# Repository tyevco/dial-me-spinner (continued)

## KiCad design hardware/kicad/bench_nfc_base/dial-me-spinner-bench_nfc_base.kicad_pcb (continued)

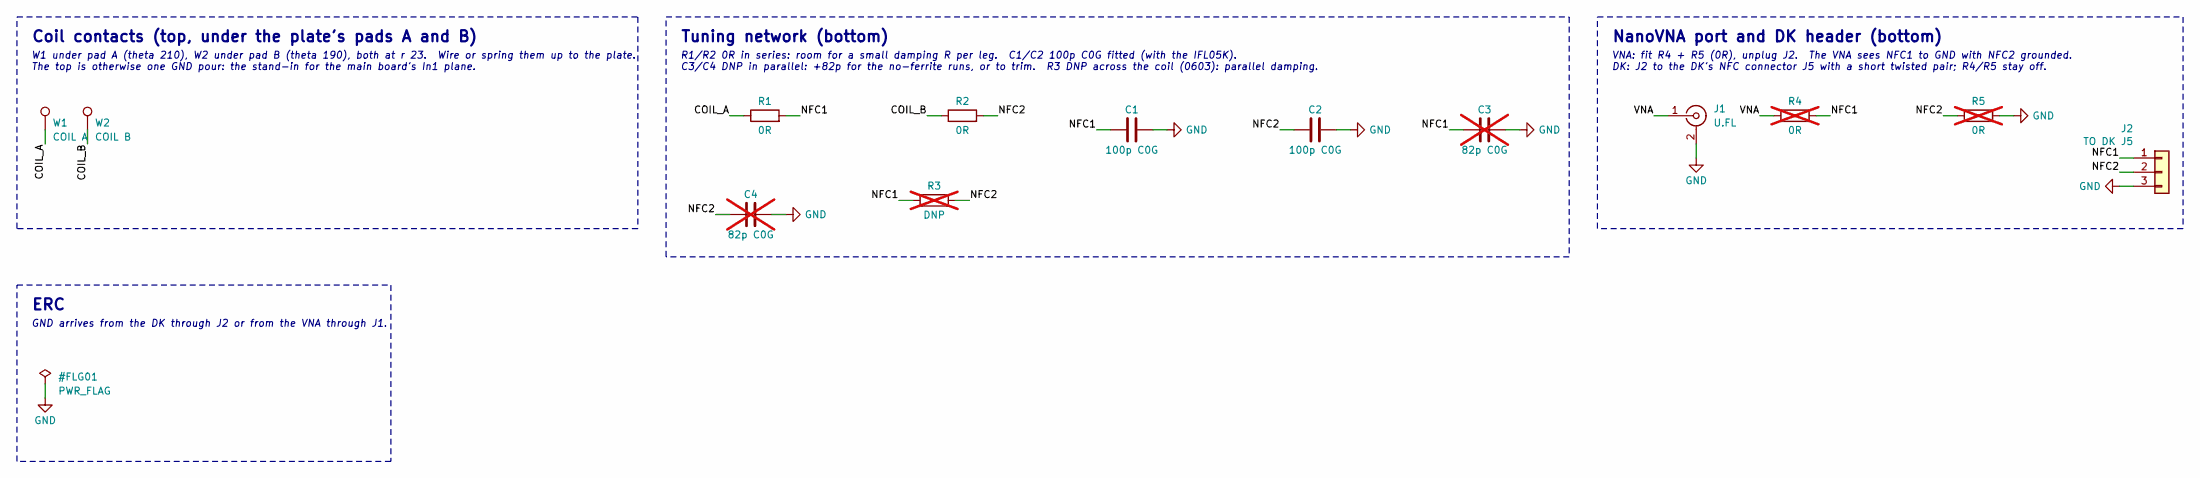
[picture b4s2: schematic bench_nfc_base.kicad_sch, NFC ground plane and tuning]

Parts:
C1, C2: 100p C0G; C_0402_1005Metric; MPN 0402CG101J500NT; LCSC C1546
C3, C4: 82p C0G; C_0402_1005Metric; MPN 0402CG820J500NT; LCSC C45501; not fitted
J1: U.FL; U.FL_Hirose_U.FL-R-SMT-1_Vertical; MPN U.FL-R-SMT-1(10); LCSC C88373
J2: TO DK J5; PinHeader_1x03_P2.54mm_Vertical
R1, R2: 0R; R_0402_1005Metric; MPN 0402WGF0000TCE; LCSC C17168
R3: DNP; R_0603_1608Metric; not fitted
R4, R5: 0R; R_0402_1005Metric; MPN 0402WGF0000TCE; LCSC C17168; not fitted
W1: COIL A; TestPoint_THTPad_2.0x2.0mm_Drill1.0mm
W2: COIL B; TestPoint_THTPad_2.0x2.0mm_Drill1.0mm

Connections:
/NFC ground plane and tuning/COIL_A: R1.1, W1.1
/NFC ground plane and tuning/COIL_B: R2.1, W2.1
/NFC ground plane and tuning/NFC1: C1.1, C3.1, J2.1, R1.2, R3.1, R4.2
/NFC ground plane and tuning/NFC2: C2.1, C4.1, J2.2, R2.2, R3.2, R5.1
/NFC ground plane and tuning/VNA: J1.1 (In), R4.1
GND: C1.2, C2.2, C3.2, C4.2, J1.2 (Ext), J2.3, R5.2

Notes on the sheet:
Coil contacts (top, under the plate's pads A and B)
W1 under pad A (theta 210), W2 under pad B (theta 190), both at r 23. Wire or spring them up to the plate. The top is otherwise one GND pour: the stand-in for the main board's In1 plane.
Tuning network (bottom)
R1/R2 0R in series: room for a small damping R per leg. C1/C2 100p C0G fitted (with the IFL05K). C3/C4 DNP in parallel: +82p for the no-ferrite runs, or to trim. R3 DNP across the coil (0603): parallel damping.
NanoVNA port and DK header (bottom)
VNA: fit R4 + R5 (0R), unplug J2. The VNA sees NFC1 to GND with NFC2 grounded. DK: J2 to the DK's NFC connector J5 with a short twisted pair; R4/R5 stay off.
ERC
GND arrives from the DK through J2 or from the VNA through J1.

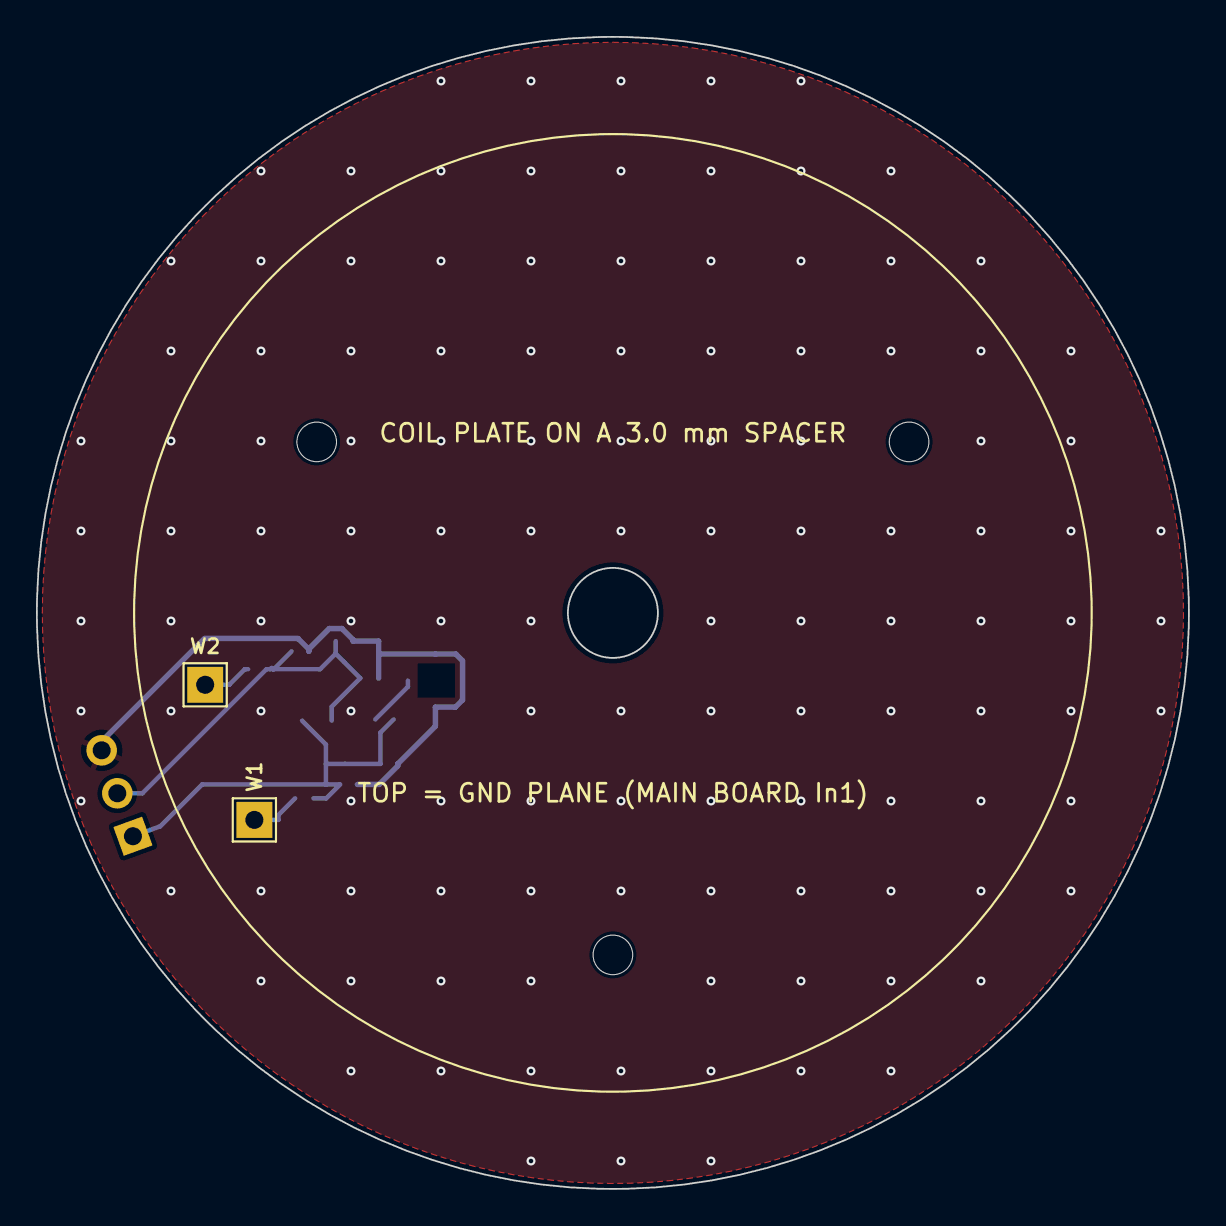
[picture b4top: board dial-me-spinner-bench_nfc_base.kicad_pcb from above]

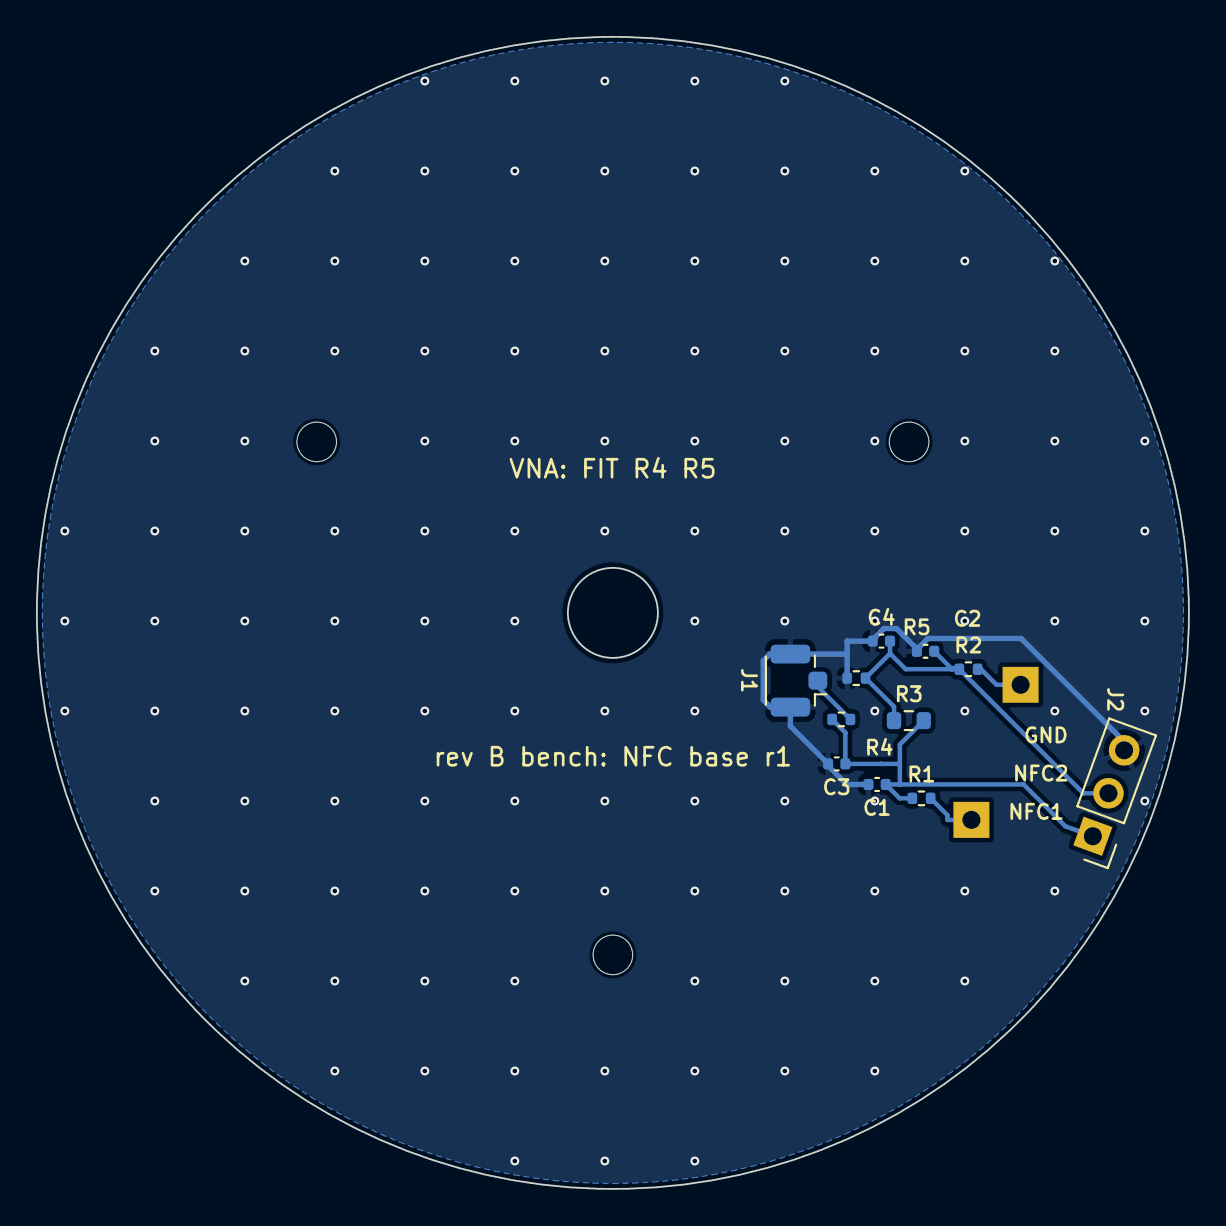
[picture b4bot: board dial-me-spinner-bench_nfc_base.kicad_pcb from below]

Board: 2 copper layers, 64.0 x 64.0 mm, 16 parts (11 on the bottom side), 6 nets.

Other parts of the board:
H1, H2, H3: MountingHole_2.2mm_M2

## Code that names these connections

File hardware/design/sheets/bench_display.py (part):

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    "16": "DISP_VBAT_EN",  # D1   P1.02  (rev A OLED_VCC_EN)
    "17": None,            # D2   P1.03
    "18": None,            # D3   P1.04
    "19": "DISP_VCI_EN",   # D4   P1.05  (rev B pin, study §7.1)
    "20": None,            # D5   P1.06
    "21": None,            # D6   P1.07
    "22": "DISP_SCK_DK",   # D7   P1.08  FULL SPEED
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    "28": None,            # D13  P1.15
    "9": None,             # A0   P0.03
    "10": "DISP_SIO0_DK",  # A1   P0.04  FULL SPEED
    "11": "TP_INT",        # A2   P0.28  (rev B pin)
    "12": "TP_RST_N",      # A3   P0.29  (rev B pin)
    "13": "DISP_SIO1",     # A4   P0.30  read-back only (ID / status at a reduced clock)
    "14": "DISP_TE",       # A5   P0.31  (rev B pin)
    "31": "I2C_SDA",       # SDA  P0.26
    "32": "I2C_SCL",       # SCL  P0.27
    "2": "VDD_DK",         # IOREF = the DK's VDD (3.0 V as shipped)
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    d.add("J1", "MCU_Module:Arduino_UNO_R3", "nRF52840-DK", "Module:Arduino_UNO_R3",
          pins=DK_PINS, in_bom=False,
          description="Arduino Uno R3 shield headers (hand-fitted stacking headers), nRF52840-DK PCA10056")
    d.add("R41", "Device:R", "0R", R0402, pins={"1": "DK_3V3", "2": "VDD_DK"}, dnp=True, fields=R0,
          description="Fit only if the DK leaves IOREF unconnected")

    d.group("Panel connector (FH26W-31S, connector pin = 32 - panel pin)",
            "Silk marks PANEL PIN 1 at connector pin 31.  Bottom contact: FPC contacts face the board.\n"
            "MTP_PWR (panel 13) open; MIPI pairs (panel 23-24, 26-27, 29-30) open.\n"
            "Decoupling at the connector pins: VBAT 10u + 100n, VCI 4.7u + 100n, IOVCC 1u + 100n, TP_VDD 1u + 100n.")
    d.add("J2", "Connector_Generic_MountingPin:Conn_01x31_MountingPin", "FH26W-31S-0.3SHW(60)", FH26_FP,
          pins={**{str(32 - p): n for p, n in PANEL_PINS.items()}, "MP": "GND"},
          datasheet=SPEC_DS,
          fields={"MPN": "FH26W-31S-0.3SHW(60)", "Manufacturer": "HIROSE", "LCSC": "C2973806"})
    d.add("C1", "Device:C", "10u", C0603, pins={"1": "DISP_VBAT", "2": "GND"}, fields=C10U)
    d.add("C2", "Device:C", "100n", C0402, pins={"1": "DISP_VBAT", "2": "GND"}, fields=C100N)
    d.add("C3", "Device:C", "4.7u", C0805, pins={"1": "VCI", "2": "GND"}, fields=C4U7)
    d.add("C4", "Device:C", "100n", C0402, pins={"1": "VCI", "2": "GND"}, fields=C100N)
    d.add("C5", "Device:C", "1u", C0402, pins={"1": "IOVCC", "2": "GND"}, fields=C1U)
    d.add("C6", "Device:C", "100n", C0402, pins={"1": "IOVCC", "2": "GND"}, fields=C100N)
    d.add("C7", "Device:C", "1u", C0402, pins={"1": "TP_VDD", "2": "GND"}, fields=C1U)
    d.add("C8", "Device:C", "100n", C0402, pins={"1": "TP_VDD", "2": "GND"}, fields=C100N)

    d.group("Panel VBAT: external source or DK VDD, through the rev B load switch",
            "J3 takes a PPK2 in source-meter mode for the 3.0-4.5 V sweep and the current-vs-content runs.\n"
            "J4 selects VBAT_IN: 1-2 = J3 (external), 2-3 = DK VDD (3.0 V, below the pin table's 3.7 V minimum).\n"
            "U1 is the TPS22917 rev B keeps (U21, renamed DISP_VBAT_EN): same CT and QOD wiring as rev A.\n"
            "R1 (DNP) bypasses U1 to rule it out.")
    d.add("J3", "Connector_Generic:Conn_01x02", "VBAT EXT", "Connector_PinHeader_2.54mm:PinHeader_1x02_P2.54mm_Vertical",
          pins={"1": "VBAT_EXT", "2": "GND"}, in_bom=False)
    d.add("J4", "Connector_Generic:Conn_01x03", "VBAT SEL", "Connector_PinHeader_2.54mm:PinHeader_1x03_P2.54mm_Vertical",
          pins={"1": "VBAT_EXT", "2": "VBAT_IN", "3": "VDD_DK"}, in_bom=False)
    d.add("U1", "Power_Management:TPS22917DBV", "TPS22917DBVR", "Package_TO_SOT_SMD:SOT-23-6",
          pins={"VIN": "VBAT_IN", "GND": "GND", "ON": "DISP_VBAT_EN", "CT": "DISP_LSW_CT",
                "QOD": "DISP_VBAT", "VOUT": "DISP_VBAT"},
          fields={"MPN": "TPS22917DBVR", "Manufacturer": "Texas Instruments", "LCSC": "C2681320"})
    d.add("C9", "Device:C", "1n", C0402, pins={"1": "DISP_LSW_CT", "2": "VBAT_IN"}, fields=C1N)
    d.add("C10", "Device:C", "10u", C0603, pins={"1": "VBAT_IN", "2": "GND"}, fields=C10U,
          description="U1 VIN bypass")
    d.add("R2", "Device:R", "100k", R0402, pins={"1": "DISP_VBAT_EN", "2": "GND"}, fields=R100K)
    d.add("R1", "Device:R", "0R", R0402, pins={"1": "VBAT_IN", "2": "DISP_VBAT"}, dnp=True, fields=R0)

    d.group("Panel logic rails from DK VDD, each separable",
            "J5 shunt carries VCI + IOVCC + TP_VDD: remove it and put a PPK2 (ammeter) across to log the logic current.\n"
            "R3-R5 split the three rails so any one can be fed or measured on its own.")
    d.add("J5", "Connector_Generic:Conn_01x02", "IDD LOGIC", "Connector_PinHeader_2.54mm:PinHeader_1x02_P2.54mm_Vertical",
          pins={"1": "VDD_DK", "2": "VDD_PANEL"}, in_bom=False)
    d.add("R3", "Device:R", "0R", R0402, pins={"1": "VDD_PANEL", "2": "VCI"}, fields=R0)
    d.add("R4", "Device:R", "0R", R0402, pins={"1": "VDD_PANEL", "2": "IOVCC"}, fields=R0)
    d.add("R5", "Device:R", "0R", R0402, pins={"1": "VDD_PANEL", "2": "TP_VDD"}, fields=R0)

    d.group("Display control and the 32 MHz lines",
            "R6/R7 0R at the header: swap for 22-33R if the SCK/SIO0 edges ring (CO5300 needs <= 3.5 ns 20-80 %).\n"
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            "DISP_RES_N 1M pull-down and DISP_VCI_EN 100k pull-down hold the panel off while the DK resets.\n"
            "SIO1 (DCX) reads back on A4, a low-frequency pin: read ID/status at a reduced clock only.\n"
            "SIO2/SIO3 are unused by the single-lane driver: 10k pull-downs, TP7/TP8 for a later QSPI test.")
    d.add("R6", "Device:R", "0R", R0402, pins={"1": "DISP_SCK_DK", "2": "DISP_SCK"}, fields=R0)
    d.add("R7", "Device:R", "0R", R0402, pins={"1": "DISP_SIO0_DK", "2": "DISP_SIO0"}, fields=R0)
    d.add("R8", "Device:R", "1M", R0402, pins={"1": "DISP_RES_N", "2": "GND"}, fields=R1M)
    d.add("R9", "Device:R", "100k", R0402, pins={"1": "DISP_VCI_EN", "2": "GND"}, fields=R100K)
    d.add("R10", "Device:R", "100k", R0402, pins={"1": "IOVCC", "2": "DISP_CS_N"}, fields=R100K)
    d.add("R11", "Device:R", "100k", R0402, pins={"1": "DISP_SIO1", "2": "GND"}, fields=R100K)
    d.add("R12", "Device:R", "10k", R0402, pins={"1": "DISP_SIO2", "2": "GND"}, fields=R10K)
    d.add("R13", "Device:R", "10k", R0402, pins={"1": "DISP_SIO3", "2": "GND"}, fields=R10K)
    for ref, net in (("TP1", "DISP_SCK"), ("TP2", "DISP_SIO0"), ("TP3", "DISP_CS_N"), ("TP4", "DISP_TE"),
                     ("TP5", "GND"), ("TP6", "GND"), ("TP7", "DISP_SIO2"), ("TP8", "DISP_SIO3")):
        d.add(ref, "Connector:TestPoint", net, TP_FP, pins={"1": net}, in_bom=False)
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            "1.8 V option (the Huaxin/Viewe drawings): remove R14/R15/R16, fit U2, U3, C11, C12, R17, R18, R19.\n"
            "In 1.8 V mode TP_INT and TP_RST_N are NOT shifted: TP_INT at 1.8 V is below the nRF's 0.7 VDD = 2.1 V\n"
            "VIH, and the nRF would drive TP_RST_N to 3.0 V.  That mode answers 'does the bus work', not 'is it done'.")
    d.add("R14", "Device:R", "0R", R0402, pins={"1": "TP_SDA", "2": "I2C_SDA"}, fields=R0)
    d.add("R15", "Device:R", "0R", R0402, pins={"1": "TP_SCL", "2": "I2C_SCL"}, fields=R0)
    d.add("R16", "Device:R", "0R", R0402, pins={"1": "VDD_PANEL", "2": "TP_VIO"}, fields=R0)
    d.add("R20", "Device:R", "4.7k", R0402, pins={"1": "VDD_DK", "2": "I2C_SDA"}, fields=R4K7)
    d.add("R21", "Device:R", "4.7k", R0402, pins={"1": "VDD_DK", "2": "I2C_SCL"}, fields=R4K7)
    d.add("R22", "Device:R", "100k", R0402, pins={"1": "TP_VIO", "2": "TP_INT"}, fields=R100K)
    d.add("R23", "Device:R", "100k", R0402, pins={"1": "TP_VIO", "2": "TP_RST_N"}, fields=R100K)
    d.add("U2", "Interface:PCA9306DC", "PCA9306DCUR", "Package_SO:VSSOP-8_2.3x2mm_P0.5mm",
          pins={"VREF1": "TP_VIO", "VREF2": "PCA_EN", "EN": "PCA_EN", "GND": "GND",
                "SCL1": "TP_SCL", "SDA1": "TP_SDA", "SCL2": "I2C_SCL", "SDA2": "I2C_SDA"},
          dnp=True, fields={"MPN": "PCA9306DCUR", "Manufacturer": "Texas Instruments", "LCSC": "C33196"})
    d.add("R17", "Device:R", "200k", R0402, pins={"1": "VDD_DK", "2": "PCA_EN"}, dnp=True, fields=R200K,
          description="PCA9306 VREF2/EN bias (datasheet: 200k to the high-side supply)")
    d.add("R18", "Device:R", "4.7k", R0402, pins={"1": "TP_VIO", "2": "TP_SDA"}, dnp=True, fields=R4K7)
    d.add("R19", "Device:R", "4.7k", R0402, pins={"1": "TP_VIO", "2": "TP_SCL"}, dnp=True, fields=R4K7)
    d.add("U3", "Regulator_Linear:AP2112K-1.8", "AP2112K-1.8TRG1", "Package_TO_SOT_SMD:SOT-23-5",
          pins={"VIN": "VDD_PANEL", "EN": "VDD_PANEL", "GND": "GND", "NC": None, "VOUT": "TP_VIO"},
          dnp=True, fields={"MPN": "AP2112K-1.8TRG1", "Manufacturer": "Diodes Incorporated", "LCSC": "C176944"})
    d.add("C11", "Device:C", "1u", C0402, pins={"1": "VDD_PANEL", "2": "GND"}, dnp=True, fields=C1U)
    d.add("C12", "Device:C", "1u", C0402, pins={"1": "TP_VIO", "2": "GND"}, dnp=True, fields=C1U)

    d.group("ERC power flags",
            "Every rail here arrives from a header or through a jumper / 0R link, which ERC cannot see as a source.")
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
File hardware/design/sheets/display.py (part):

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def build(d):
    d.sheet(*SHEET)
    # Layout notes (generator-specific): 2-pin parts whose pins carry long power names
    # (+13V_OLED, OLED_VIN) are drawn vertical (rot=0) with the long name on the bottom pin;
    # vertical parts alternate with horizontal ones so their side fields never collide.

    # ------------------------------------------------------------------ panel
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          fields={"MPN": "AFC01-S30FCA-00", "Manufacturer": "JUSHUO", "LCSC": "C262671",
                  "Mates_With": "NHD-1.5-128128G (Newhaven) / AOC128128A0-1.50W (Orient)",
                  "Panel_Datasheet": NHD_DS})
    d.add("R20", "Device:R", "1M", R0402, pins={"1": "OLED_RES_N", "2": "GND"},
          fields={"MPN": "0402WGF1004TCE", "Manufacturer": "UNI-ROYAL", "LCSC": "C26083"})
    d.add("#FLG21", "power:PWR_FLAG", "PWR_FLAG", "", pins={"1": "+13V_OLED"}, in_bom=False, on_board=False)

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            "C39 = boost output cap on +13V_OLED: place it at D21 / U20 GND, not at the ZIF.\n"
            "No bleeders or QOD switches on +3V3 / +13V_OLED (VCC must float when off).", 182))
    d.add("C32", "Device:C_Polarized", "4.7u/25V Ta", "Capacitor_Tantalum_SMD:CP_EIA-3216-18_Kemet-A",
          pins={"1": "OLED_VCOMH", "2": "GND"},
          description="VCOMH (FPC pin 3) tantalum, + to VCOMH",
          fields={"MPN": "TAJA475K025RNJ", "Manufacturer": "KYOCERA AVX", "LCSC": "C7189"})
    d.add("C30", "Device:C", "10u/25V", C0805, rot=0, pins={"1": "GND", "2": "+13V_OLED"},
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    d.add("C31", "Device:C", "100n/50V", C0402, rot=0, pins={"1": "GND", "2": "+13V_OLED"},
          description="VCC (FPC pin 2) HF decoupling",
          fields={"MPN": "CL05B104KB54PNC", "Manufacturer": "Samsung Electro-Mechanics", "LCSC": "C307331"})
    d.add("C34", "Device:C", "1u", C0402, pins={"1": "OLED_VDD", "2": "GND"},
          description="VDD (FPC pin 26, internal regulator output)",
          fields={"MPN": "CL05A105KA5NQNC", "Manufacturer": "Samsung Electro-Mechanics", "LCSC": "C52923"})
    d.add("C39", "Device:C", "4.7u/25V", C0805, rot=0, pins={"1": "GND", "2": "+13V_OLED"},
          description="Boost output capacitor (place at D21 cathode / U20 GND)",
          fields={"MPN": "CL21A475KAQNNNE", "Manufacturer": "Samsung Electro-Mechanics", "LCSC": "C1779"})
    d.add("C35", "Device:C", "4.7u/25V", C0805, pins={"1": "GND", "2": "+3V3"},
          description="VCI (FPC pin 27) bulk",
          fields={"MPN": "CL21A475KAQNNNE", "Manufacturer": "Samsung Electro-Mechanics", "LCSC": "C1779"})
    d.add("C36", "Device:C", "100n", C0402, rot=0, pins={"1": "GND", "2": "+3V3"},
          description="VCI (FPC pin 27) HF decoupling",
          fields={"MPN": "CL05B104KO5NNNC", "Manufacturer": "Samsung Electro-Mechanics", "LCSC": "C1525"})

    d.group("IREF and VSL networks",
            "IREF: R = (VCC - 6 V) / 12.5 uA = 560k at 13 V (recompute if VCC changes).\n"
            "VSL: 50 ohm 1/4 W + ~1.4 V: BAV99 as 2 series diodes (pin 1 A1, pin 3 mid NC, pin 2 K2).")
    d.add("R21", "Device:R", "560k", R0402, pins={"1": "OLED_IREF", "2": "GND"},
          fields={"MPN": "0402WGF5603TCE", "Manufacturer": "UNI-ROYAL", "LCSC": "C132339"})
    d.add("R22", "Device:R", "51R 1/4W", R1206, pins={"1": "OLED_VSL", "2": "OLED_VSL_D"},
          fields={"MPN": "1206W4F510JT5E", "Manufacturer": "UNI-ROYAL", "LCSC": "C18019"})
    d.add("D20", "Diode:BAV99", "BAV99", SOT23,
          pins={"1": "OLED_VSL_D", "2": "GND", "3": None},
          fields={"MPN": "BAV99,215", "Manufacturer": "Nexperia", "LCSC": "C2500"})

    # ------------------------------------------------------------------ boost
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            "(Replaces the AO3401A/2N7002 disconnect, which had no real dV/dt control - review SCH-1.)\n"
            "LAYOUT: L20 and the SW node >= 10 mm from the TMAG5273 and the magnet track.", 180))
    d.add("U21", "Power_Management:TPS22917DBV", "TPS22917DBVR", "Package_TO_SOT_SMD:SOT-23-6",
          pins={"VIN": "VSYS", "GND": "GND", "ON": "OLED_VCC_EN", "CT": "OLED_LSW_CT", "QOD": "OLED_VIN", "VOUT": "OLED_VIN"},
          fields={"MPN": "TPS22917DBVR", "Manufacturer": "Texas Instruments", "LCSC": "C2681320"})
    d.add("C37", "Device:C", "1n/50V", C0402, pins={"1": "OLED_LSW_CT", "2": "VSYS"},
          fields={"MPN": "0402B102K500NT", "Manufacturer": "FH", "LCSC": "C1523"})
    d.add("C41", "Device:C", "10u/25V", "Capacitor_SMD:C_0603_1608Metric", pins={"1": "VSYS", "2": "GND"},
          description="U21 VIN bypass",
          fields={"MPN": "CL10A106MA8NRNC", "Manufacturer": "Samsung Electro-Mechanics", "LCSC": "C96446"})
    d.add("C38", "Device:C", "4.7u/25V", C0805, rot=0, pins={"1": "GND", "2": "OLED_VIN"},
          description="Boost input capacitor (place at U20 VIN/GND)",
          fields={"MPN": "CL21A475KAQNNNE", "Manufacturer": "Samsung Electro-Mechanics", "LCSC": "C1779"})
    d.add("R25", "Device:R", "100k", R0402, pins={"1": "OLED_VCC_EN", "2": "GND"},
          fields={"MPN": "0402WGF1003TCE", "Manufacturer": "UNI-ROYAL", "LCSC": "C25741"})
    d.add("L20", "Device:L", "10u", "Inductor_SMD:L_Sunlord_SWPA3015S",
          rot=0, pins={"1": "OLED_BST_SW", "2": "OLED_VIN"},
          fields={"MPN": "SWPA3015S100MT", "Manufacturer": "Sunlord", "LCSC": "C45403"})

    d.group("13 V boost: TPS61040, rectifier, FB divider", _pad(
            "VOUT = 1.233 V x (1 + 499k / 52.3k) = 13.00 V (0.5 % / 0.1 % divider); CFF C40 33 pF across R26 (tune 22-100 pF).\n"
            "EN tied to OLED_VIN: the input disconnect does the switching.  L 10 uH, Isat 0.72 A rated (0.92 A typ; peak need 0.49 A).\n"
            "LAYOUT: tight CIN-L-SW-GND and SW-D-COUT-GND loops; R26/R27/C40 at the FB pin, away from SW.", 150))
    d.add("R27", "Device:R", "52.3k 0.1%", R0402, pins={"1": "GND", "2": "OLED_BST_FB"},
          fields={"MPN": "RT0402BRD0752K3L", "Manufacturer": "YAGEO", "LCSC": "C852832"})
    d.add("R26", "Device:R", "499k 0.5%", R0402, rot=0, pins={"1": "OLED_BST_FB", "2": "+13V_OLED"},
          fields={"MPN": "RC0402DR-07499KL", "Manufacturer": "YAGEO", "LCSC": "C4167968"})
    d.add("U20", "Regulator_Switching:TPS61040DBV", "TPS61040DBVR", "Package_TO_SOT_SMD:SOT-23-5",
          pins={"VIN": "OLED_VIN", "EN": "OLED_VIN", "GND": "GND", "SW": "OLED_BST_SW", "FB": "OLED_BST_FB"},
          datasheet=TPS_DS,
          fields={"MPN": "TPS61040DBVR", "Manufacturer": "Texas Instruments", "LCSC": "C7722"})
    d.add("C40", "Device:C", "33p C0G", C0402, rot=0, pins={"1": "OLED_BST_FB", "2": "+13V_OLED"},
          fields={"MPN": "0402CG330J500NT", "Manufacturer": "FH (Fenghua)", "LCSC": "C1562"})
    d.add("D21", "dial_spinner:B5819W_SOD123", "B5819W", "Diode_SMD:D_SOD-123",
          pins={"A": "OLED_BST_SW", "K": "+13V_OLED"},
          fields={"MPN": "B5819W SL", "Manufacturer": "Jiangsu Changjing (CJ)", "LCSC": "C8598"})

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
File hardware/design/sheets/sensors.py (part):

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    d.add("C51", "Device:C", "1u", C0402, pins={"1": "GND", "2": "+3V3"},
          fields={"MPN": "CL05A105KA5NQNC", "Manufacturer": "Samsung Electro-Mechanics", "LCSC": "C52923"})
    d.add("U30", "dial_spinner:TMAG5273", "TMAG5273A2QDBVR", "Package_TO_SOT_SMD:SOT-23-6",
          pins={"1": "TMAG_SCL", "6": "TMAG_SDA", "5": "TMAG_INT_N", "4": "+3V3", "2": "GND", "3": "GND"},
          fields={"MPN": "TMAG5273A2QDBVR", "Manufacturer": "Texas Instruments", "LCSC": "C3715882"})

    d.group("Encoder ESD (floating 316L ring 2.4 mm below)",
            "The flywheel is a touchable, electrically floating metal ring passing under U30.\n"
            "U32 clamps TMAG_SCL/SDA/INT_N right at U30 (short GND return via next to U30).")
    d.add("U32", "Power_Protection:TPD4E05U06DQA", "TPD4E05U06DQAR", "Package_SON:USON-10_2.5x1.0mm_P0.5mm",
          pins={"1": "TMAG_SCL", "2": "TMAG_SDA", "4": "TMAG_INT_N", "5": None, "3": "GND",
                "6": None, "7": None, "9": None, "10": None},
          fields={"MPN": "TPD4E05U06DQAR", "Manufacturer": "Texas Instruments", "LCSC": "C138714"},
          datasheet="https://www.ti.com/lit/ds/symlink/tpd4e05u06.pdf")

    d.group("Encoder bus pull-ups (dedicated TWIM0)",
            "4.7k SCL/SDA; 47k on open-drain INT (10 us pulses / latched)")
    d.add("R50", "Device:R", "4.7k", R0402, pins={"1": "+3V3", "2": "TMAG_SCL"},
          fields={"MPN": "0402WGF4701TCE", "Manufacturer": "UNI-ROYAL", "LCSC": "C25900"})
    d.add("R51", "Device:R", "4.7k", R0402, pins={"1": "+3V3", "2": "TMAG_SDA"},
          fields={"MPN": "0402WGF4701TCE", "Manufacturer": "UNI-ROYAL", "LCSC": "C25900"})
    d.add("R52", "Device:R", "47k", R0402, pins={"1": "+3V3", "2": "TMAG_INT_N"},
          fields={"MPN": "0402WGF4702TCE", "Manufacturer": "UNI-ROYAL", "LCSC": "C25792"})

    # ---------------------------------------------------------------- IMU
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    d.add("C54", "Device:C", "100n", C0402, pins={"1": "GND", "2": "+3V3"},
          fields={"MPN": "CL05B104KO5NNNC", "Manufacturer": "Samsung Electro-Mechanics", "LCSC": "C1525"})
    d.add("U31", "dial_spinner:LIS2DW12", "LIS2DW12TR", "Package_LGA:LGA-12_2x2mm_P0.5mm",
          pins={"1": "I2C_SCL", "4": "I2C_SDA", "2": "+3V3", "3": "+3V3",
                "12": "IMU_INT1", "11": "IMU_INT2", "5": None,
                "9": "+3V3", "10": "+3V3", "6": "GND", "8": "GND", "7": "GND"},
          fields={"MPN": "LIS2DW12TR", "Manufacturer": "STMicroelectronics", "LCSC": "C189624"})
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    # ---------------------------------------------------------------- pull-ups
    d.group("System I2C + link signal pull-ups (the only ones on the board)",
            "System I2C goes to IMU + BQ25180 (0x6A, via link). CHG_INT_N / BTN_N are open drain on the base board.")
    d.add("R53", "Device:R", "4.7k", R0402, pins={"1": "+3V3", "2": "I2C_SCL"},
          fields={"MPN": "0402WGF4701TCE", "Manufacturer": "UNI-ROYAL", "LCSC": "C25900"})
    d.add("R54", "Device:R", "4.7k", R0402, pins={"1": "+3V3", "2": "I2C_SDA"},
          fields={"MPN": "0402WGF4701TCE", "Manufacturer": "UNI-ROYAL", "LCSC": "C25900"})
    d.add("R55", "Device:R", "10k", R0402, pins={"1": "+3V3", "2": "CHG_INT_N"},
          fields={"MPN": "0402WGF1002TCE", "Manufacturer": "UNI-ROYAL", "LCSC": "C25744"})
    d.add("R56", "Device:R", "100k", R0402, pins={"1": "+3V3", "2": "BTN_N"},
          fields={"MPN": "0402WGF1003TCE", "Manufacturer": "UNI-ROYAL", "LCSC": "C25741"})

    # ---------------------------------------------------------------- piezo
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            "Complementary PWM on BUZZ_A/BUZZ_B (one nRF PWM instance): +/-3.3 Vo-p (max +/-12.5).\n"
            "Murata land pattern: two 1.3 x 3.4 mm pads at x = +/-4.35 mm (custom footprint).\n"
            "Sound exits via 2 mm slots in the bottom face at the non-terminal edges: keep them clear.")
    d.add("R57", "Device:R", "470", R0402, pins={"1": "BUZZ_A", "2": "BZ_P"},
          fields={"MPN": "0402WGF4700TCE", "Manufacturer": "UNI-ROYAL", "LCSC": "C25117"})
    d.add("R58", "Device:R", "470", R0402, pins={"1": "BUZZ_B", "2": "BZ_N"},
          fields={"MPN": "0402WGF4700TCE", "Manufacturer": "UNI-ROYAL", "LCSC": "C25117"})
    d.add("R59", "Device:R", "1M", R0402, pins={"1": "BZ_P", "2": "BZ_N"},
          description="Bleeds piezo charge from shock while the drive pins are disconnected in sleep",
          fields={"MPN": "0402WGF1004TCE", "Manufacturer": "UNI-ROYAL", "LCSC": "C26083"})
    d.add("BZ1", "Device:Speaker_Crystal", "PKMCS0909E4000-R1", "dial_spinner:" + PIEZO_FP,
          pins={"1": "BZ_P", "2": "BZ_N"},
          datasheet=PIEZO_DS, description="Murata 4 kHz SMD piezo sounder, external drive, 9x9x1.9 mm",
          fields={"MPN": "PKMCS0909E4000-R1", "Manufacturer": "Murata", "LCSC": "C910763"})

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
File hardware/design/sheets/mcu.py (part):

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            "REG1 DC/DC on (its inductor is inside the module).\n"
            "u.FL on module -> Molex 146153-0100 flex antenna.\n"
            "Pin map = nets.MCU_PINS (SPEC §4).\n"
            "UICR: P0.18 = nRESET; NFCPINS stays in NFC mode\n"
            "(P0.09/P0.10 = NFC1/NFC2 antenna).\n"
            "Symbol: stock MDBT50Q-U1MV2 pins, regrouped by port.")
    d.add("U10", "dial_spinner:" + MCU_SYM, "MDBT50Q-U1MV2", MCU_FP,
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            "U12 USBLC6 at the module: IEC 8 kV on D+/D- otherwise drives 2.6-3.7 A into the nRF pads through the\n"
            "~145 nH link (HBM 2 kV class = 1.33 A). U12 as close as the module courtyard allows (3.1 mm pad\n"
            "centre to D- pad centre); test_usb_input reads the placed distance.")
    d.add("R12", "Device:R", "4.7", R0402, pins={"1": "VBUS", "2": "VBUS_NRF"},
          fields={"MPN": "FRC0402F4R70TS", "Manufacturer": "FOJAN", "LCSC": "C2909356"})
    d.add("C12", "Device:C", "4.7u/16V", C0603, pins={"1": "VBUS_NRF", "2": "GND"}, rot=0,
          fields={"MPN": "CL10A475KO8NNNC", "Manufacturer": "Samsung Electro-Mechanics", "LCSC": "C19666"})
    d.add("U12", "Power_Protection:USBLC6-2SC6", "USBLC6-2SC6", "Package_TO_SOT_SMD:SOT-23-6",
          pins={"1": "USB_DP", "6": "USB_DP", "3": "USB_DM", "4": "USB_DM", "5": "VBUS_NRF", "2": "GND"},
          fields={"MPN": "USBLC6-2SC6", "Manufacturer": "STMicroelectronics", "LCSC": "C7519"})
    # VBUS_NRF is fed from the flagged VBUS through R12; ERC does not propagate a supply through a resistor.
    d.add("#FLG10", "power:PWR_FLAG", "PWR_FLAG", "", pins={"1": "VBUS_NRF"}, in_bom=False, on_board=False)

    d.group("32.768 kHz LFXO", "SC-20S CL 9 pF; Ccap = 2*CL - Cpin - Cpcb ~ 12 pF C0G.\n"
            "R1 <= 90k (nRF RS_LFXO max 100k); DLmax 0.5 uW = nRF PD_LFXO.\n"
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            "-IQ suffix: QE=1 fixed, /WP and /HOLD disabled, so IO2/IO3 need no pull-ups.\n"
            "CS pulled up so the flash stays deselected in reset. Use deep power-down when idle.")
    d.add("U11", "Memory_Flash:W25Q128JVS", "W25Q128JVSIQ", "Package_SO:SOIC-8_5.3x5.3mm_P1.27mm",
          pins={"1": "QSPI_CS", "2": "QSPI_IO1", "3": "QSPI_IO2", "4": "GND",
                "5": "QSPI_IO0", "6": "QSPI_SCK", "7": "QSPI_IO3", "8": "+3V3"},
          datasheet="https://www.winbond.com/resource-files/w25q128jv%20revf%2003272018%20plus.pdf",
          fields={"MPN": "W25Q128JVSIQ", "Manufacturer": "Winbond", "LCSC": "C97521"})
    d.add("C15", "Device:C", "100n", C0402, pins={"1": "+3V3", "2": "GND"},
          fields={"MPN": "CL05B104KO5NNNC", "Manufacturer": "Samsung Electro-Mechanics", "LCSC": "C1525"})
    d.add("R10", "Device:R", "10k", R0402, pins={"1": "+3V3", "2": "QSPI_CS"},
          fields={"MPN": "0402WGF1002TCE", "Manufacturer": "UNI-ROYAL", "LCSC": "C25744"})

    d.group("SWD debug (Tag-Connect TC2030-NL)",
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            "R11 is a DNP option.")
    d.add("J10", "Connector:Conn_ARM_SWD_TagConnect_TC2030-NL", "SWD",
          "Connector:Tag-Connect_TC2030-IDC-NL_2x03_P1.27mm_Vertical",
          pins={"1": "+3V3", "2": "SWDIO", "3": "NRESET", "4": "SWDCLK", "5": "GND", "6": "SWO"},
          fields={"MPN": "TC2030-IDC-NL (footprint only)", "Manufacturer": "Tag-Connect"},
          in_bom=False)
    d.add("R11", "Device:R", "10k", R0402, pins={"1": "+3V3", "2": "NRESET"}, dnp=True,
          fields={"MPN": "0402WGF1002TCE", "Manufacturer": "UNI-ROYAL", "LCSC": "C25744"})

    d.group("NFC tag antenna (nRF52840 NFCT, NFC-A Type 2/4)",
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            "Tune: Ctune = 2/((2*pi*13.56 MHz)^2 * L_coil) - Cp - Cint (Cint ~ 4 pF, PS 6.13);\n"
            "180 pF C0G each suits L ~ 1.4-1.5 uH; retune on prototype.\n"
            "Route NFC1/NFC2 as a pair, away from the TMAG and the LED data line.")
    d.add("C16", "Device:C", "180p C0G", C0402, pins={"1": "NFC1", "2": "GND"},
          fields={"MPN": "0402CG181J500NT", "Manufacturer": "FH (Guangdong Fenghua)", "LCSC": "C78636"})
    d.add("C17", "Device:C", "180p C0G", C0402, pins={"1": "NFC2", "2": "GND"},
          fields={"MPN": "0402CG181J500NT", "Manufacturer": "FH (Guangdong Fenghua)", "LCSC": "C78636"})
    d.add("J11", "Connector_Generic:Conn_01x02", "NFC_COIL", "dial_spinner:" + NFC_FP,
          pins={"1": "NFC1", "2": "NFC2"}, in_bom=False,
          description="Solder pads for the NFC coil flex tail (no part fitted)")

    d.group("Spare GPIO test pads", "Value = module GPIO\n(P0.03/P0.04 = AIN1/AIN2)")
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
